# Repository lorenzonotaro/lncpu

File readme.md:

# lncpu

LNCPU is a design for a hobby 8-bit processor. 

## Project structure

Overview of the repository:
* [`v1`](v1) is the first implementation of the lncpu. Here you will find the Logisim simulation and the KiCad project (currently under construction), as well as the Python script for generating the control unit EEPROMS.

* [`lnc`](lnc) is an assembler and C compiler written in Java for the lncpu. It is kept up to date with the current implementation.

* [`eeprom-serial-loader`](eeprom-serial-loader) is a utility program for editing binary data and loading it to/from EEPROMS.

* [`lncpu-emu`](lncpu-emu) is a simple emulator for the lncpu written in C.

* [`lnfsutils`](lnfsutils) is a utility program for working with the lnfs filesystem, a simple FS designed to work on the lncpu.

* [`Programs`](Programs) contains some sample programs you can assemble and run on the lncpu as well as Notmon, a utility program strongly inspired in its functionality (and name) by Wozmon, made by Steve Wozniak for his Apple I.

* [`extras`](extras) contains some additional tools, such as a VsCode extension for lnasm.

## Current state of the project

* **Physical implementation**: work in progress. The Logisim simulation is basically done and tested. Some adjustments to the architecture may still be made, but the main design is complete. The KiCad project is under construction, and it might be necessary to properly simulate the design with actual hardware simulation software (e.g. an HDL simulation) before implementing it physically.

* **Assembler and C compiler**: the assembler is basically complete and stable. The C compiler is still a work in progress, but it is already usable for small-medium sized programs. Arrays and structs are yet to be implemented. The register allocator is very basic and can be improved and general optimization passes in the various stages would be very beneficial for an inefficient architecture like this one.

* **EEPROM editor and loader**: the utility is basically complete and stable. Some improvements can be made to the UI, but it is already usable. More loaders other than the AT28C64 can be added.

* **Emulator**: The emulator is also basically done, but it is very basic and can be improved a lot. It is currently Windows-only because of the use of `<conio.h>` for keyboard input, but porting it to Linux or MacOS should be easy.

* **Programs**: A simple BIOS for the lncpu is under development. Notmon is basically complete and stable, but more features can be added.

* **Extras**: The VsCode extension has syntax highlighting and basic symbol support for lnasm files. More features can be added, such as code snippets and integration with lnc.

## Building

### Prerequisites

- [Maven](https://maven.apache.org/) and [JDK 16+](https://www.oracle.com/java/technologies/javase/jdk16-archive-downloads.html) are required for building both `lnc` and `eeprom-serial-loader`.
- [Python 3.x](https://www.python.org/downloads/) is required to generate the EEPROMs for the control unit.
- [Logisim-evolution](https://github.com/logisim-evolution/logisim-evolution) is used to simulate the design.
- Any C compiler and [CMake](https://cmake.org/) to build the emulator (e.g. `gcc`).

**Note**: I suggest using [my fork of Logisim-evolution (logisim-lncpu branch)](https://github.com/lorenzonotaro/logisim-evolution/tree/lncpu-debugger-logisim) to open the Logisim project. It includes useful features like:
- testing environment for the lncpu
- easy loading of all CU EEPROMs at once
- a neat LNCPU debugger

If you're on Linux, `make.sh` will build everything for you. Usage:

    ./make.sh [--no-eeproms] [--no-eeprom-serial-loader|--no-esl] [--no-lnc] [--no-lnfs|--no-lnfs-utils]

If you're on Windows, use `make.bat` instead. Usage:

    ./make.bat [--no-eeproms] [--no-eeprom-serial-loader|--no-esl] [--no-lnc] [--no-lnfs|--no-lnfs-utils]

These scripts will create an `output` folder containing:
- `lnc.jar`: the assembler and C compiler along with `lnc.bat`/`lnc.sh` scripts for easy usage
- `eeprom-serial-loader.jar`: the EEPROM editing and loading utility along with `eeprom-serial-loader.bat`/`eeprom-serial-loader.sh` scripts for easy usage
- `lncpu-emu.exe`: the LNCPU emulator executable
- `eeproms`: a folder containing all the generated control unit EEPROMs (if you have my fork of Logisim, you may open the Logisim project, then go to Simulate -> Debug LNCPU -> Load CU EEPROMS and select this folder to load them all at once).
- a `lib` folder containing libraries for lnc/lnasm

It is recommended to add the `output` folder to your PATH environment variable for easy usage of `lnc` and `eeprom-serial-loader` from any location and allow the Logisim debugger to compile and load programs directly.

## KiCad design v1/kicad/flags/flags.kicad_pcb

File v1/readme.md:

_This page is a work in progress._

# lncpu v1

v1 is the current implementation of the lncpu.

## Clock cycle

The clock cycle is divided in two phases: Φ1 (control phase) and Φ2 (data phase).

* During Φ1, the data bus contains the contents of `[CS:PC]`: only the device mapped to the memory section containing address `CS:PC` is allowed to write to the data bus, regardless of control signals.

* During Φ2, bus control is determined by the control signals of the current microinstruction.

Each phase has a clock pulse entirely within it, and components may synchronize at the rising edge or the falling edge of each clock pulse.

From Φ and the base clock, 4 rising edges are derived:
* **C1** (Φ1), _control_: the next instruction or microinstruction is loaded and the control signals are stabilized.
* **C2** (Φ1), _fetch_: if required by the current microinstruction, data is moved from `[CS:PC]` to the data latch register via the data bus.
* **C3** (Φ2), _data_: data is transferred between the activated components via the data bus.
* **C4** (Φ2), _increment_: counters such as `CS:PC`, `SP` are incremented/decremented as specified by the current microinstruction.

# Pipeline

The implementation uses a very simple pipeline to spare a few clock cycles.

1. At the beginning of the first clock cycle of any instruction (i.e. when Φ1 goes high), the following conditions are required: 

    * `Data latch (DL)` must contain the **value of the instruction about to be executed**.
    * `CS:PC` must contain the the address of the byte **after the opcode about to be executed**.

*Every instruction (including break, jump and call instructions) must pass to the next with this configuration*.

2. During the execution of the instruction:

    1. `Data latch (DL)` will be loaded with the value pointed to by `CS:PC` (i.e. either the next opcode or the next byte to be fetched by the instruction), then
    2. `CS:PC` will be incremented to point to the byte that will be fetched during the next clock cycle.

# General purpose registers
The CPU has 4 general-purpose 8-bit registers, named `RA`, `RB`, `RC`, and `RD`. These registers can be used to store data and are used by most instructions.

Some registers have special purposes:
* `RA` has left and right shift capabilities, and is used by the `shl` and `shr` instructions.
* `RC` and `RD` are used in combination with the `ircrd` addressing mode to read and write data from the address space.
* `RD` is the only register that can be used to read and write dynamic data to and from `SS`, `SP` and `BP` registers (this is due to the limited number of opcodes available with a 1-byte instruction).

# Jump instructions
The CPU supports several jump instructions that allow the program to change the flow of execution. Each instruction (except `lcall`) is available in two variants, a short and a long variant. The short variant uses a 1-byte immediate value as the target address and loads it into `PC` (without touching `CS`), while the long variant uses a 2-byte absolute address as the target address and loads it into `CS:PC`. 
Short jumps require one less clock cycle than long jumps, so they are preferred when the target address is known at compile time and is within the same code segment as the jump instruction.

The jump instructions are:
| Instruction | Short variant | Long variant | Description |
|-------------|---------------|--------------|-------------|
| Go to | `goto` | `lgoto` | Jumps to the specified address. |
| Jump if carry | `jc` | `ljc` | Jumps to the specified address if the carry flag is set. |
| Jump if zero | `jz` | `ljz` | Jumps to the specified address if the zero flag is set. |
| Jump if negative | `jn` | `ljn` | Jumps to the specified address if the negative flag is set. |
| Call | *not available* | `lcall` | Jumps to the specified address and pushes the current `CS:PC` onto the stack. |

# ALU and FLAGS

The CPU has a simple arithmetic logic unit (ALU) that can perform basic arithmetic and logical operations. The ALU can perform the following operations:
| Operation | Description |
|-----------|-------------|
| `add`     | Adds the contents of two registers or a register and an immediate value. |
| `sub`     | Subtracts the contents of two registers or a register and an immediate value. |
| `and`     | Performs a bitwise AND operation on the contents of two registers or a register and an immediate value. |
| `or`      | Performs a bitwise OR operation on the contents of two registers or a register and an immediate value. |
| `xor`     | Performs a bitwise XOR operation on the contents of two registers or a register and an immediate value. |
| `not`     | Performs a bitwise NOT operation on the contents of a register. |
| `shl`     | Shifts the contents of a register left by 1 bit (multiplying by 2). Only available for `RA`. |
| `shr`     | Shifts the contents of a register right by 1 bit (dividing by 2). Only available for `RA`. |
| `inc`     | Increments the contents of a register by 1. |
| `dec`     | Decrements the contents of a register by 1. |

The ALU also sets the `FLAGS` register based on the result of the operation. The `FLAGS` register is a 4-bit register that contains the following flags (least significant bit first):
| Flag | Description |
|------|-------------|
| `C` | Carry flag, set to 1 if the result of an addition or subtraction operation causes an overflow. |
| `Z` | Zero flag, set to 1 if the result of an operation is 0. |
| `N` | Negative flag, set to 1 if the result of an operation is negative (i.e. the most significant bit is set). |
| `I` | Interrupt disable flag, set to 1 if interrupts are disabled (not modified by ALU operations) |

The `CZN` flags can be used to control the flow of the program with conditional jump instructions. The `I` flag is used to enable or disable interrupts, as described in the [Interrupts](#interrupts) section.

The `C` flag can be manually set or cleared with the `sec` (set carry) and `clc` (clear carry) instructions, respectively.

# Address space
The address bus is 16-bits wide, allowing for a total of 65536 bytes of addressable memory. The address space is divided in 8 "devices"; the top 3 bits of the address bus are used to select the device, while the bottom 13 bits are used to select the address within that device.
The address space is divided as follows:
| Device | Address range | Description |
|--------|---------------|-------------|
| ROM    | 0x0000 - 0x1FFF | Read-only memory, points to the extractable chip that can be loaded with a program. |
| RAM    | 0x2000 - 0x3FFF | Read-write memory, used for data storage. |
| D0     | 0x4000 - 0x5FFF | Device 1, can be used for any purpose. |
| D1     | 0x6000 - 0x7FFF | Device 2, can be used for any purpose. |
| D2     | 0x8000 - 0x9FFF | Device 3, can be used for any purpose. |
| D3     | 0xA000 - 0xBFFF | Device 4, can be used for any purpose. |
| D4     | 0xC000 - 0xDFFF | Device 5, can be used for any purpose. |
| D5     | 0xE000 - 0xFFFF | Device 6, can be used for any purpose. |

# Stack

The implementation includes a basic stack setup:

* the 8-bit `SS` register contains the page that will contain the stack (i.e. the top 8-bits of the current stack pointer).

* the 8-bit `SP` register points to the **next available stack position** in the stack page.

The top of the stack is pointed to by `SS:SP`. The stack **grows upwards**: `push` operations move a value into `[SS:SP]` and increment the stack by 1; `pop` operations read the value from `[SS:SP]` and decrement the stack by 1.

Calls and interrupts will push the current `CS:PC` onto the stack, so that it can be restored later. It is the programmer's responsibility to load `SS` and `SP` with correct values before using stack manipulation instructions and/or calls, and to ensure that the stack does not overflow, as the implementation does not include any stack overflow checks.

To function properly, the stack obviously needs to be located in a location in the address space that is writable and readable by the CPU (usually in memory, but it can also be in any device that supports reading and writing). See the [Address space](#address-space) section for more information.

The `BP` register points to the base of the current stack frame. It is not updated along with SP, so it can be used to access local variables in the current stack frame. It is the programmer's responsibility to ensure that `BP` is set correctly before using it.
It is used by some instructions to access local variables in the current stack frame, with an addressing mode known as `ibpoffset` (base pointer offset, e.g. `[BP+1]` to access the first local variable in the current stack frame).

# Data segment
The data segment is a 256-byte segment that is used to store frequently used data by some instructions that use `dpage` addressing mode and that require one less clock cycle. 
The `DS` register points to the data segment, containing the top 8-bits of the data segment's start address.
The data segment can be located anywhere in the address space, but it is recommended to place it in the RAM device (0x2000 - 0x3FFF) to ensure that it is writable and readable by the CPU.

# Interrupts
The implementation includes a basic interrupt system that allows the CPU to handle interrupts from devices.

Devices can signal an interrupt by pulling the `~IRQ` line low. Instead of loading the next instruction, at the end of the current instruction, the CPU will push the current `CS:PC` and the current `FLAGS` register value onto the stack and load the `CS:PC` with the value `0x1F00` (the interrupt vector address, last page of ROM). This is the address where the interrupt handler is located, and it is the programmer's responsibility to ensure that the interrupt handler is loaded there.

The interrupt handler is a piece of code that will handle the interrupt and return control to the CPU when it is done via the `iret` instruction.
The interrupt handler must detect which device signaled the interrupt and handle it accordingly and must communicate with that device to acknowledge the interrupt and clear it (otherwise the device will keep signaling the interrupt and the CPU will keep handling it, causing an infinite loop).

Interrupts can be disabled with the `sid` (set interrupt disable) instruction, which will set the `I` flag in the `FLAGS` register to 1. This will prevent the CPU from handling interrupts until the `cid` (clear interrupt disable) instruction is executed, which will clear the `I` flag in the `FLAGS` register to 0.

# Addressing modes
The CPU supports several addressing modes, which determine how the operands of an instruction are accessed. The addressing modes are:
| Addressing mode | Name | Description |
|-----------------|------|-------------|
| `immediate`     | Immediate | The operand is a constant value, specified as an operand to the instruction. |
| `abs`        | Absolute | The operand is a 2-byte address of a location in the address space, provided as an operand to the instruction. |
| `dpage`      | Data page | The operand is a 1-byte offset (specified as an operand to the instruction) from the data segment, which is specified in the `DS` register. |
| `ibpoffset`  | Stack frame | The operand is a 1-byte offset (specified as an operand to the instruction) from the stack base pointer, which is specified in the `BP` register. |
| `ird`        | Data page indirect | Requires no operands, the location is in the data page at the address specified by the contents of the `RD` register. |
| `ircrd` | Full indirect | Requires no operands, the location is specified by the contents of the RC and RD registers.

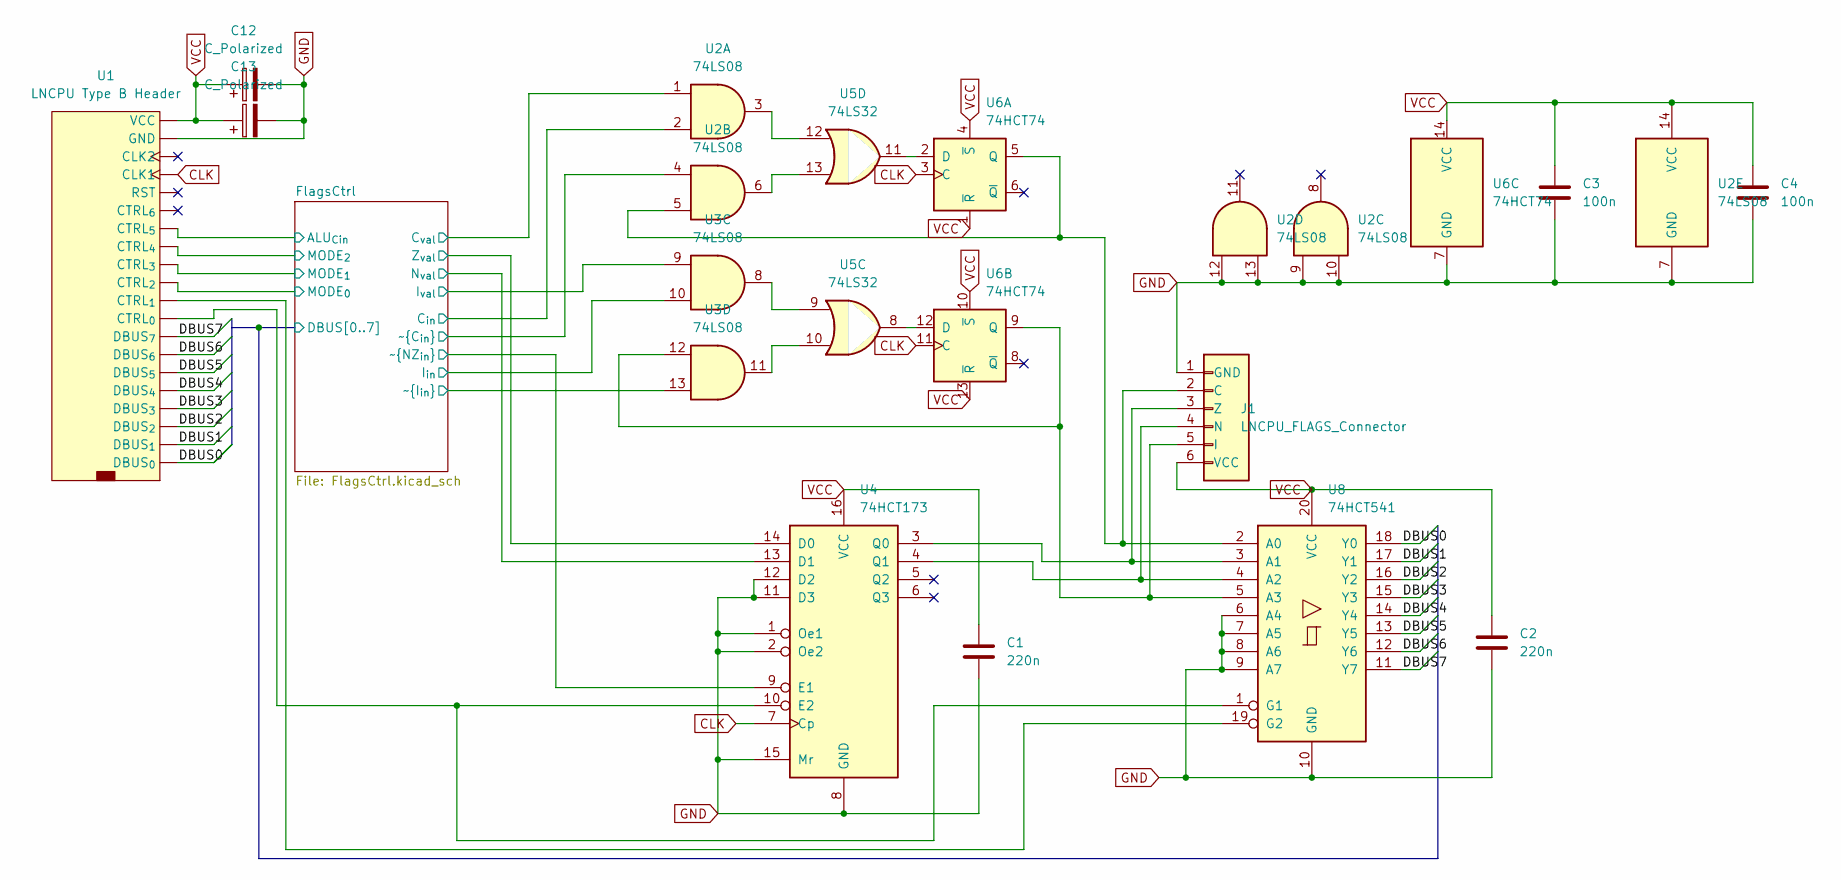
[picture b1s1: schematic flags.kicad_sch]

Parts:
C1, C2: 220n; C_Disc_D5.0mm_W2.5mm_P2.50mm
C3, C4: 100n; C_Disc_D5.0mm_W2.5mm_P2.50mm
C12: C_Polarized; CP_Radial_D5.0mm_P2.00mm
C13: C_Polarized; CP_Radial_D4.0mm_P2.00mm-Large-Holes
J1: LNCPU_FLAGS_Connector; PinSocket_1x06_P2.54mm_Vertical
U1: LNCPU Type B Header; LNCPU_Type_B_Header
U2, U3: 74LS08; DIP-14_W7.62mm_LongPads
U4: 74HCT173; DIP-16_W7.62mm_LongPads
U5: 74LS32; DIP-14_W7.62mm_LongPads
U6: 74HCT74; DIP-14_W7.62mm_LongPads
U8: 74HCT541; DIP-20_W7.62mm_LongPads

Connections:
/FlagsCtrl/ALU_{Cin}: U1.14 (CTRL_{5}); also elsewhere on the board
/FlagsCtrl/C_{val}: U2.1; also elsewhere on the board
/FlagsCtrl/DBUS0: U1.3 (DBUS_{0}), U8.18 (Y0); also elsewhere on the board
/FlagsCtrl/DBUS1: U1.5 (DBUS_{1}), U8.17 (Y1); also elsewhere on the board
/FlagsCtrl/DBUS2: U1.7 (DBUS_{2}), U8.16 (Y2); also elsewhere on the board
/FlagsCtrl/DBUS3: U1.9 (DBUS_{3}), U8.15 (Y3); also elsewhere on the board
/FlagsCtrl/DBUS4: U1.11 (DBUS_{4}), U8.14 (Y4); also elsewhere on the board
/FlagsCtrl/DBUS5: U1.13 (DBUS_{5}), U8.13 (Y5); also elsewhere on the board
/FlagsCtrl/DBUS6: U1.15 (DBUS_{6}), U8.12 (Y6); also elsewhere on the board
/FlagsCtrl/DBUS7: U1.17 (DBUS_{7}), U8.11 (Y7); also elsewhere on the board
/FlagsCtrl/I_{in}: U3.10; also elsewhere on the board
/FlagsCtrl/I_{val}: U3.9; also elsewhere on the board
/FlagsCtrl/MODE_{0}: U1.8 (CTRL_{2}); also elsewhere on the board
/FlagsCtrl/MODE_{1}: U1.10 (CTRL_{3}), U2.2; also elsewhere on the board
/FlagsCtrl/MODE_{2}: U1.12 (CTRL_{4}); also elsewhere on the board
/FlagsCtrl/N_{val}: U4.13 (D1); also elsewhere on the board
/FlagsCtrl/Z_{val}: U4.14 (D0); also elsewhere on the board
/FlagsCtrl/~I_{in}: U3.13; also elsewhere on the board
/FlagsCtrl/~MODE_{1}: U2.4; also elsewhere on the board
/FlagsCtrl/~NZ_{in}: U4.9 (E1); also elsewhere on the board
CLK: U1.21 (CLK1), U4.7 (Cp), U6.3 (C), U6.11 (C)
GND: C1.2, C2.2, C3.2, C4.2, C12.2, C13.2, J1.1 (GND), U1.1 (GND), U1.18 (GND), U1.22 (GND), U1.23 (GND), U2.7 (GND), U2.9, U2.10, U2.12, U2.13, U4.1 (Oe1), U4.2 (Oe2), U4.8 (GND), U4.11 (D3), U4.12 (D2), U4.15 (Mr), U6.7 (GND), U8.6 (A4), U8.7 (A5), U8.8 (A6), U8.9 (A7), U8.10 (GND); also elsewhere on the board
unnamed: J1.2 (C), U2.5, U6.5 (Q), U8.2 (A0)
unnamed: J1.5 (I), U3.12, U6.9 (Q), U8.5 (A3)
unnamed: J1.4 (N), U4.4 (Q1), U8.4 (A2)
unnamed: J1.3 (Z), U4.3 (Q0), U8.3 (A1)
unnamed: U1.4 (CTRL_{0}), U4.10 (E2), U8.1 (G1)
unnamed: U1.6 (CTRL_{1}), U8.19 (G2)
unnamed: U2.3, U5.12
unnamed: U2.6, U5.13
unnamed: U3.8, U5.9
unnamed: U3.11, U5.10
unnamed: U5.11, U6.2 (D)
unnamed: U5.8, U6.12 (D)
VCC: C1.1, C2.1, C3.1, C4.1, C12.1, C13.1, J1.6 (VCC), U1.2 (VCC), U1.24 (VCC), U2.14 (VCC), U4.16 (VCC), U6.1 (~R), U6.4 (~S), U6.10 (~S), U6.13 (~R), U6.14 (VCC), U8.20 (VCC); also elsewhere on the board

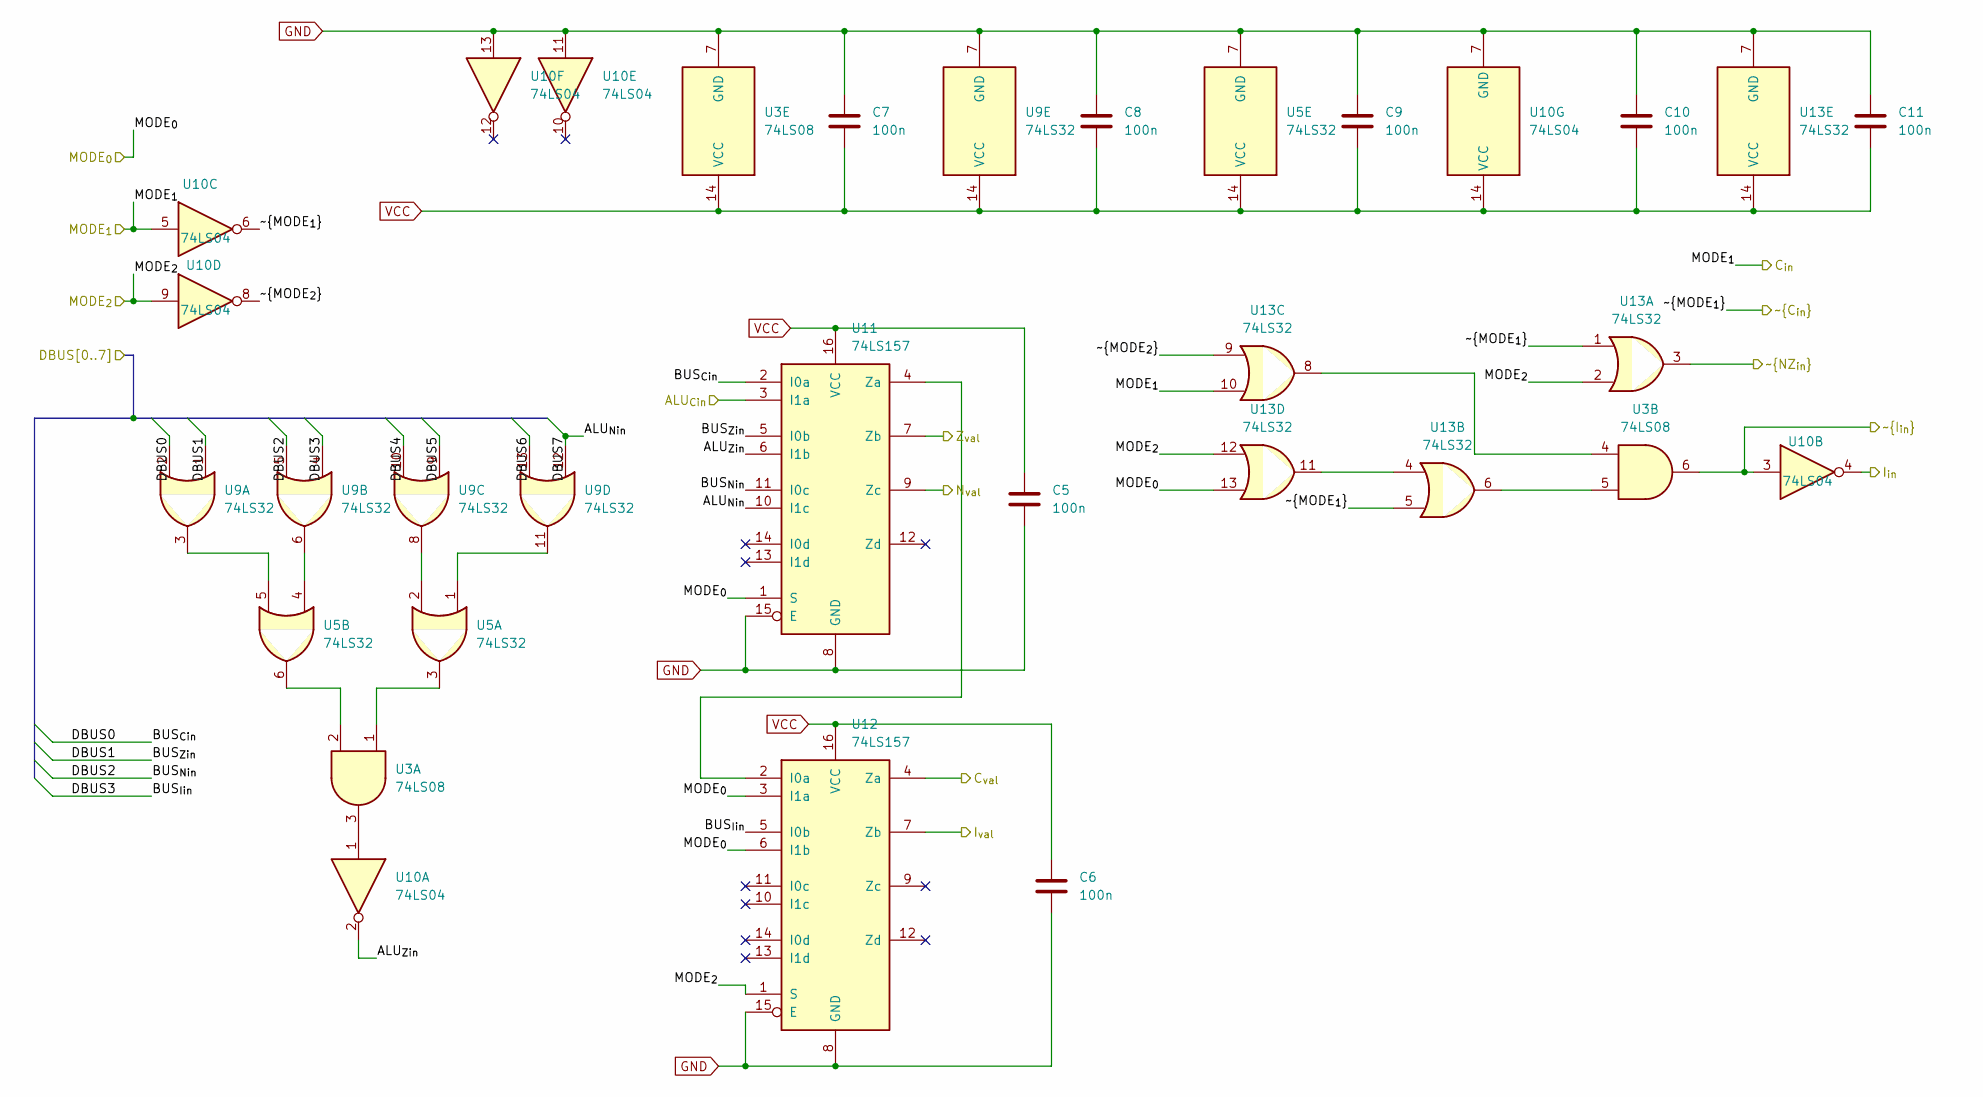
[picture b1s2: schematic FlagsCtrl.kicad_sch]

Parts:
C5, C6, C7, C8, C9, C10, C11: 100n; C_Disc_D5.0mm_W2.5mm_P2.50mm
U3: 74LS08; DIP-14_W7.62mm_LongPads
U5, U9, U13: 74LS32; DIP-14_W7.62mm_LongPads
U10: 74LS04; DIP-14_W7.62mm_LongPads
U11, U12: 74LS157; DIP-16_W7.62mm_LongPads

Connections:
/FlagsCtrl/ALU_{Cin}: U11.3 (I1a); also elsewhere on the board
/FlagsCtrl/ALU_{Zin}: U10.2, U11.6 (I1b)
/FlagsCtrl/C_{val}: U12.4 (Za); also elsewhere on the board
/FlagsCtrl/DBUS0: U9.2, U11.2 (I0a); also elsewhere on the board
/FlagsCtrl/DBUS1: U9.1, U11.5 (I0b); also elsewhere on the board
/FlagsCtrl/DBUS2: U9.5, U11.11 (I0c); also elsewhere on the board
/FlagsCtrl/DBUS3: U9.4, U12.5 (I0b); also elsewhere on the board
/FlagsCtrl/DBUS4: U9.10; also elsewhere on the board
/FlagsCtrl/DBUS5: U9.9; also elsewhere on the board
/FlagsCtrl/DBUS6: U9.13; also elsewhere on the board
/FlagsCtrl/DBUS7: U9.12, U11.10 (I1c); also elsewhere on the board
/FlagsCtrl/I_{in}: U10.4; also elsewhere on the board
/FlagsCtrl/I_{val}: U12.7 (Zb); also elsewhere on the board
/FlagsCtrl/MODE_{0}: U11.1 (S), U12.3 (I1a), U12.6 (I1b), U13.13; also elsewhere on the board
/FlagsCtrl/MODE_{1}: U10.5, U13.10; also elsewhere on the board
/FlagsCtrl/MODE_{2}: U10.9, U12.1 (S), U13.2, U13.12; also elsewhere on the board
/FlagsCtrl/N_{val}: U11.9 (Zc); also elsewhere on the board
/FlagsCtrl/Z_{val}: U11.7 (Zb); also elsewhere on the board
/FlagsCtrl/~I_{in}: U3.6, U10.3; also elsewhere on the board
/FlagsCtrl/~MODE_{1}: U10.6, U13.1, U13.5; also elsewhere on the board
/FlagsCtrl/~MODE_{2}: U10.8, U13.9
/FlagsCtrl/~NZ_{in}: U13.3; also elsewhere on the board
GND: C5.2, C6.2, C7.1, C8.1, C9.1, C10.1, C11.1, U3.7 (GND), U5.7 (GND), U9.7 (GND), U10.7 (GND), U10.11, U10.13, U11.8 (GND), U11.15 (E), U12.8 (GND), U12.15 (E), U13.7 (GND); also elsewhere on the board
unnamed: U3.1, U5.3
unnamed: U3.2, U5.6
unnamed: U5.1, U9.11
unnamed: U5.2, U9.8
unnamed: U5.4, U9.6
unnamed: U5.5, U9.3
unnamed: U3.3, U10.1
unnamed: U11.4 (Za), U12.2 (I0a)
unnamed: U3.5, U13.6
unnamed: U3.4, U13.8
unnamed: U13.4, U13.11
VCC: C5.1, C6.1, C7.2, C8.2, C9.2, C10.2, C11.2, U3.14 (VCC), U5.14 (VCC), U9.14 (VCC), U10.14 (VCC), U11.16 (VCC), U12.16 (VCC), U13.14 (VCC); also elsewhere on the board

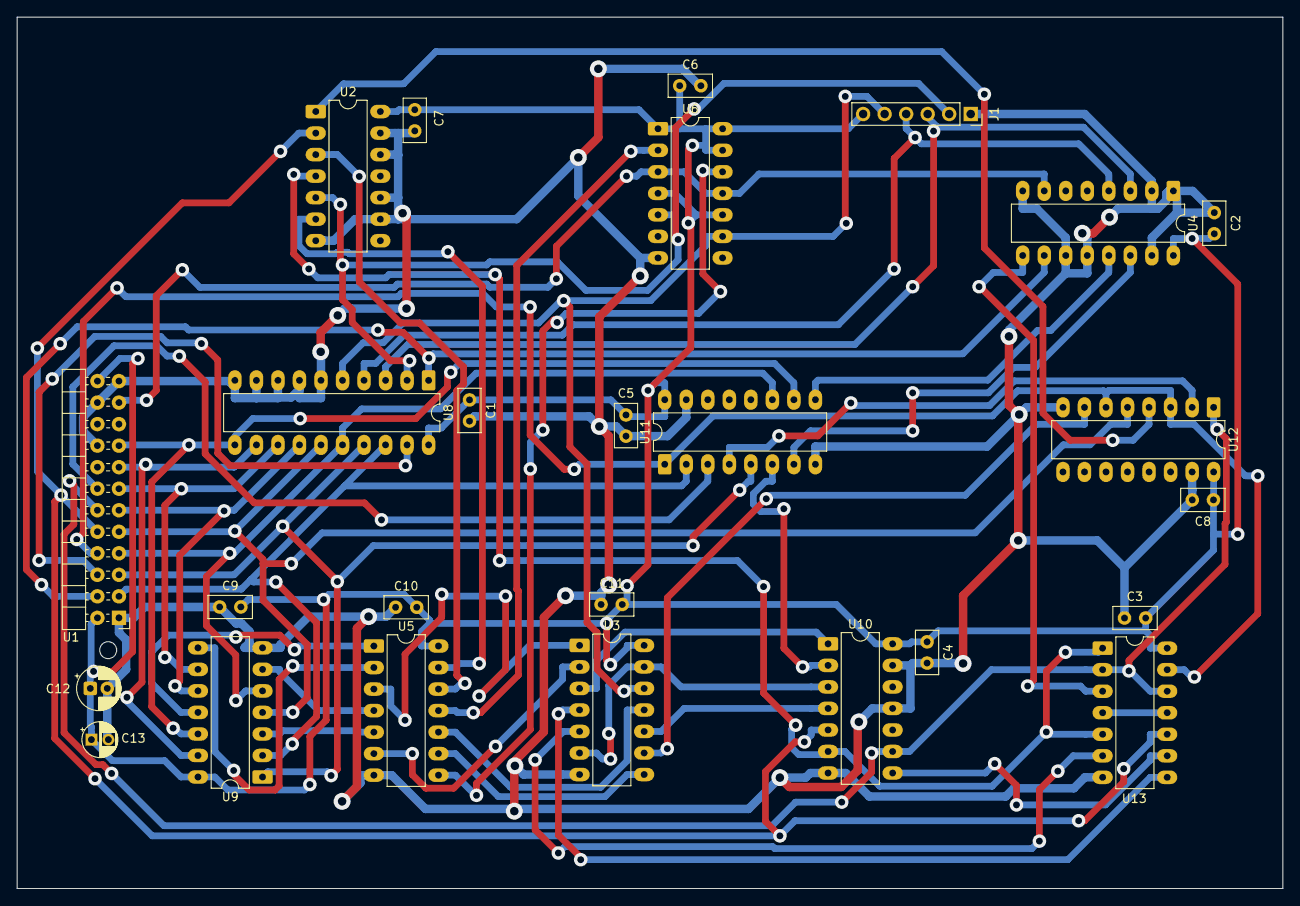
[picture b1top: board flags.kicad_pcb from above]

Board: 2 copper layers, 149.4 x 102.8 mm, 26 parts (0 on the bottom side), 48 nets.

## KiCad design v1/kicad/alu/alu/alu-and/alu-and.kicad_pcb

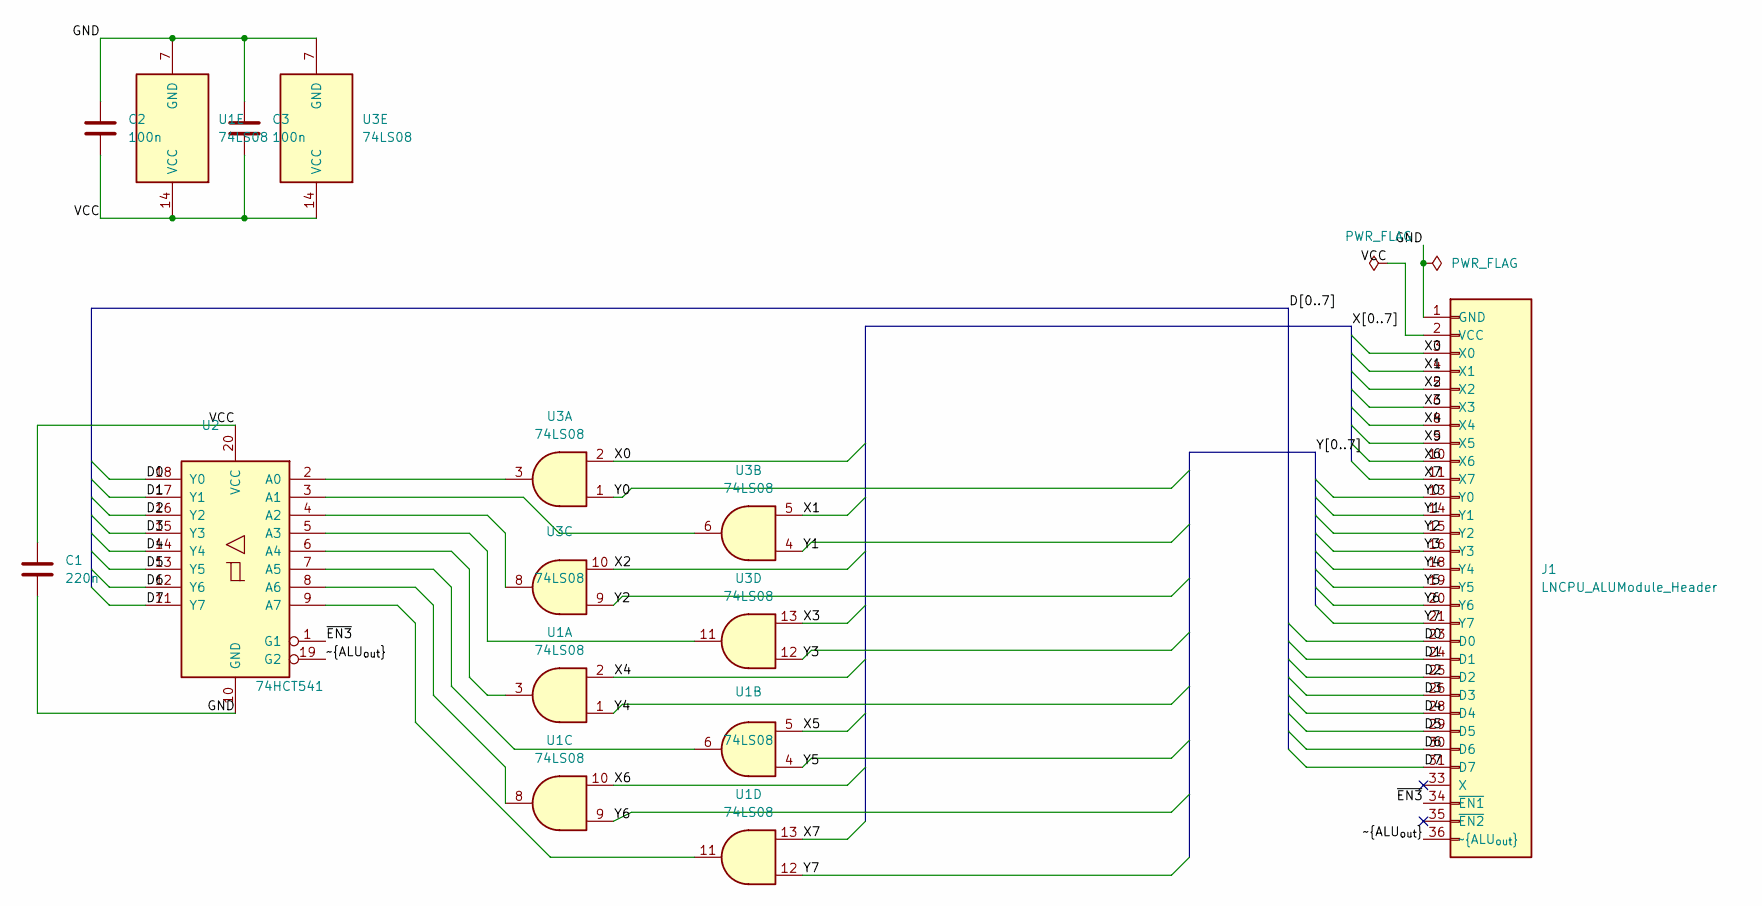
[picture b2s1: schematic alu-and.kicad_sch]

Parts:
C1: 220n; C_Disc_D5.0mm_W2.5mm_P5.00mm
C2, C3: 100n; C_Disc_D5.0mm_W2.5mm_P5.00mm
J1: LNCPU_ALUModule_Header; LNCPU_ALU_Module_Header
U1, U3: 74LS08; DIP-14_W7.62mm_LongPads
U2: 74HCT541; DIP-20_W7.62mm_LongPads

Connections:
/D0: J1.23 (D0), U2.18 (Y0)
/D1: J1.24 (D1), U2.17 (Y1)
/D2: J1.25 (D2), U2.16 (Y2)
/D3: J1.26 (D3), U2.15 (Y3)
/D4: J1.28 (D4), U2.14 (Y4)
/D5: J1.29 (D5), U2.13 (Y5)
/D6: J1.30 (D6), U2.12 (Y6)
/D7: J1.31 (D7), U2.11 (Y7)
/GND: C1.2, C2.1, C3.1, J1.1 (GND), J1.7 (GND), J1.12 (GND), J1.17 (GND), J1.22 (GND), J1.27 (GND), J1.32 (GND), J1.37 (GND), U1.7 (GND), U2.10 (GND), U3.7 (GND)
/VCC: C1.1, C2.2, C3.2, J1.2 (VCC), J1.38 (VCC), U1.14 (VCC), U2.20 (VCC), U3.14 (VCC)
/X0: J1.3 (X0), U3.2
/X1: J1.4 (X1), U3.5
/X2: J1.5 (X2), U3.10
/X3: J1.6 (X3), U3.13
/X4: J1.8 (X4), U1.2
/X5: J1.9 (X5), U1.5
/X6: J1.10 (X6), U1.10
/X7: J1.11 (X7), U1.13
/Y0: J1.13 (Y0), U3.1
/Y1: J1.14 (Y1), U3.4
/Y2: J1.15 (Y2), U3.9
/Y3: J1.16 (Y3), U3.12
/Y4: J1.18 (Y4), U1.1
/Y5: J1.19 (Y5), U1.4
/Y6: J1.20 (Y6), U1.9
/Y7: J1.21 (Y7), U1.12
/~ALU_{out}: J1.36 (~ALU_{out}), U2.19 (G2)
/~EN3: J1.34 (~EN1), U2.1 (G1)
unnamed: U2.2 (A0), U3.3
unnamed: U2.3 (A1), U3.6
unnamed: U2.4 (A2), U3.8
unnamed: U2.5 (A3), U3.11
unnamed: U1.3, U2.6 (A4)
unnamed: U1.6, U2.7 (A5)
unnamed: U1.8, U2.8 (A6)
unnamed: U1.11, U2.9 (A7)

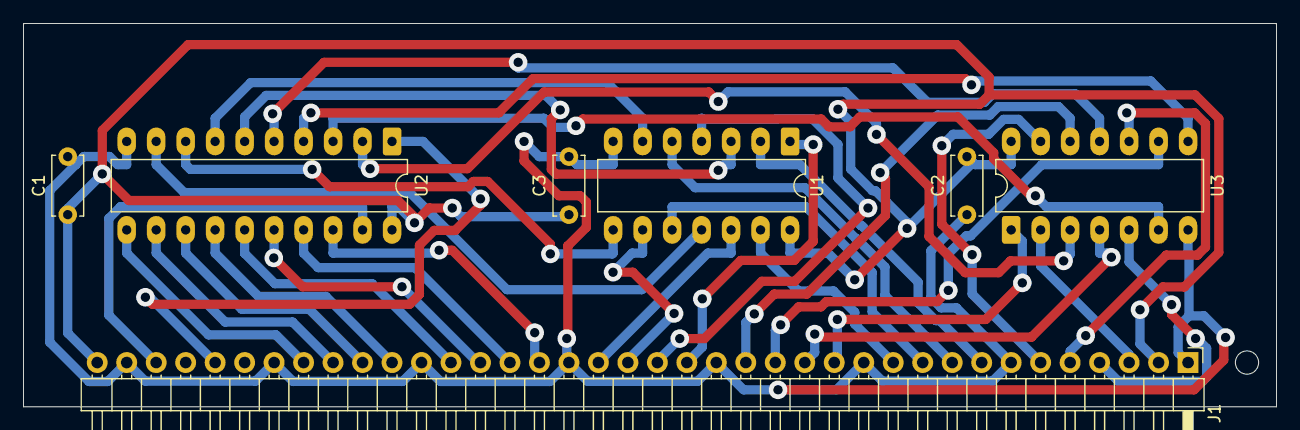
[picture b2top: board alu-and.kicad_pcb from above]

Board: 2 copper layers, 108.0 x 33.0 mm, 7 parts (0 on the bottom side), 36 nets.

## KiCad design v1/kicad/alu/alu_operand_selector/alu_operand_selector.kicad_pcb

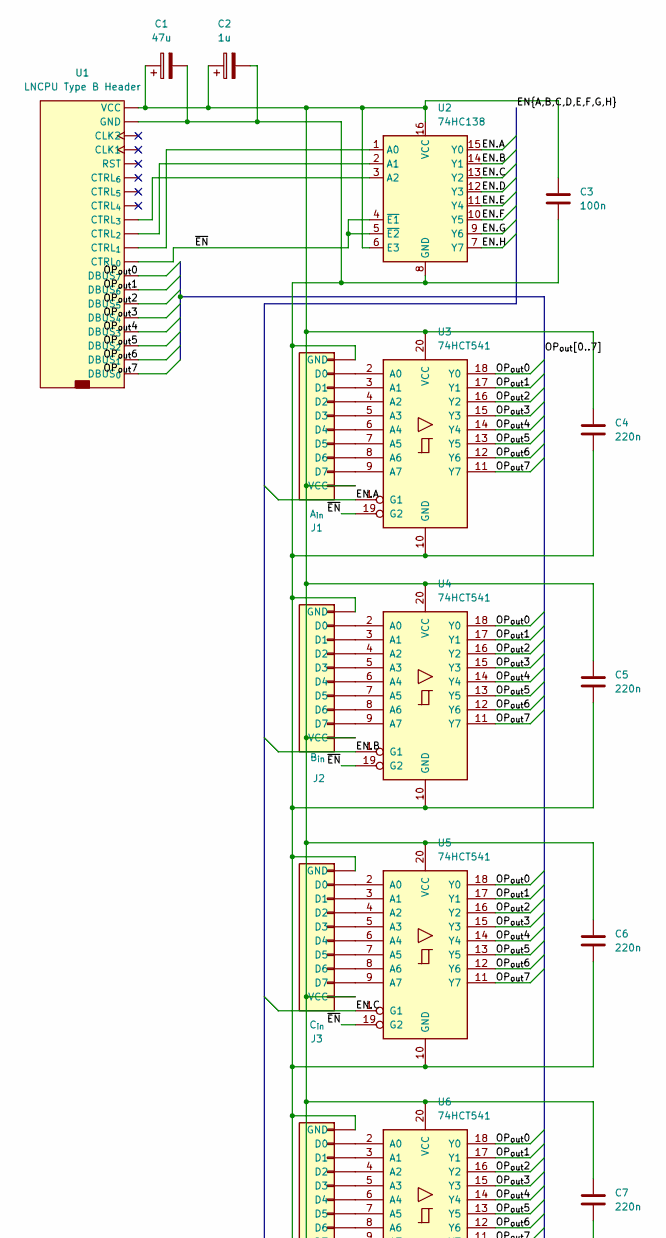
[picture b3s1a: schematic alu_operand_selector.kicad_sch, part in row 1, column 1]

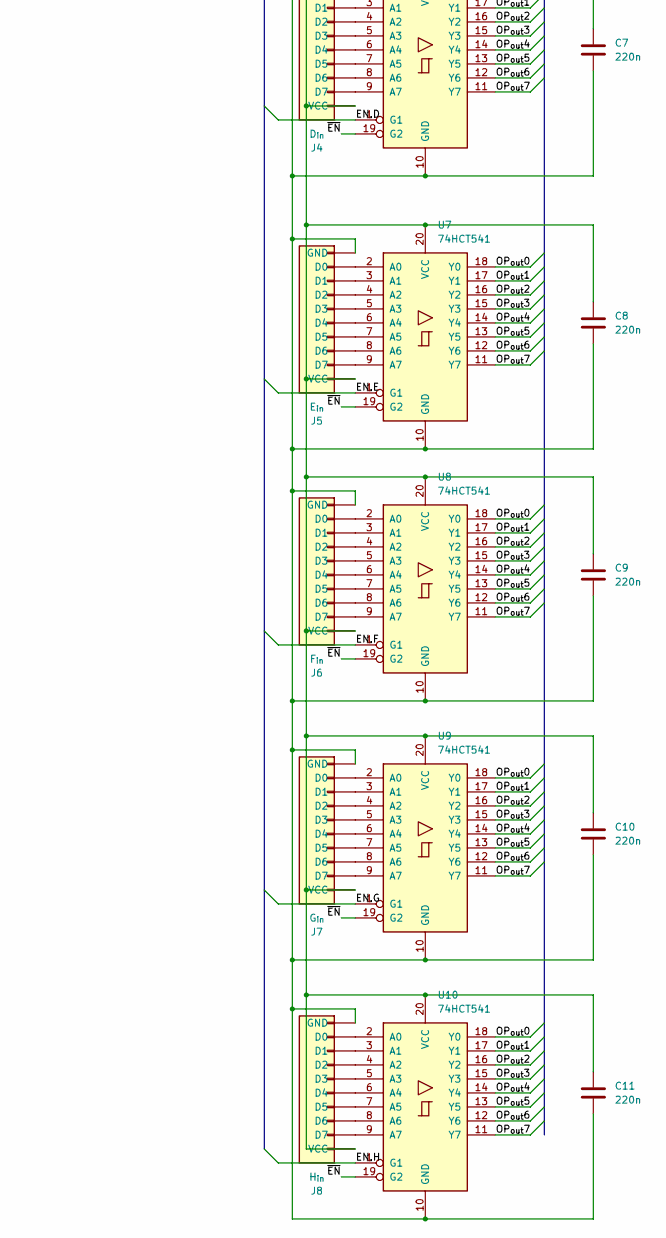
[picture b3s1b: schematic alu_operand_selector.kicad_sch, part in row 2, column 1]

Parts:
C1: 47u; CP_Radial_D5.0mm_P2.00mm
C2: 1u; CP_Radial_D4.0mm_P2.00mm-Large-Holes
C3: 100n; C_Disc_D5.0mm_W2.5mm_P2.50mm
C4, C5, C6, C7, C8, C9, C10, C11: 220n; C_Disc_D5.0mm_W2.5mm_P2.50mm
J1: A_{in}; PinSocket_1x10_P2.54mm_Vertical
J2: B_{in}; PinSocket_1x10_P2.54mm_Vertical
J3: C_{in}; PinSocket_1x10_P2.54mm_Vertical
J4: D_{in}; PinSocket_1x10_P2.54mm_Vertical
J5: E_{in}; PinSocket_1x10_P2.54mm_Vertical
J6: F_{in}; PinSocket_1x10_P2.54mm_Vertical
J7: G_{in}; PinSocket_1x10_P2.54mm_Vertical
J8: H_{in}; PinSocket_1x10_P2.54mm_Vertical
U1: LNCPU Type B Header; LNCPU_Type_B_Header
U2: 74HC138; DIP-16_W7.62mm_LongPads
U3, U4, U5, U6, U7, U8, U9, U10: 74HCT541; DIP-20_W7.62mm_LongPads

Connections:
/EN.A: U2.15 (Y0), U3.1 (G1)
/EN.B: U2.14 (Y1), U4.1 (G1)
/EN.C: U2.13 (Y2), U5.1 (G1)
/EN.D: U2.12 (Y3), U6.1 (G1)
/EN.E: U2.11 (Y4), U7.1 (G1)
/EN.F: U2.10 (Y5), U8.1 (G1)
/EN.G: U2.9 (Y6), U9.1 (G1)
/EN.H: U2.7 (Y7), U10.1 (G1)
/OP_{out}0: U1.17 (DBUS_{7}), U3.18 (Y0), U4.18 (Y0), U5.18 (Y0), U6.18 (Y0), U7.18 (Y0), U8.18 (Y0), U9.18 (Y0), U10.18 (Y0)
/OP_{out}1: U1.15 (DBUS_{6}), U3.17 (Y1), U4.17 (Y1), U5.17 (Y1), U6.17 (Y1), U7.17 (Y1), U8.17 (Y1), U9.17 (Y1), U10.17 (Y1)
/OP_{out}2: U1.13 (DBUS_{5}), U3.16 (Y2), U4.16 (Y2), U5.16 (Y2), U6.16 (Y2), U7.16 (Y2), U8.16 (Y2), U9.16 (Y2), U10.16 (Y2)
/OP_{out}3: U1.11 (DBUS_{4}), U3.15 (Y3), U4.15 (Y3), U5.15 (Y3), U6.15 (Y3), U7.15 (Y3), U8.15 (Y3), U9.15 (Y3), U10.15 (Y3)
/OP_{out}4: U1.9 (DBUS_{3}), U3.14 (Y4), U4.14 (Y4), U5.14 (Y4), U6.14 (Y4), U7.14 (Y4), U8.14 (Y4), U9.14 (Y4), U10.14 (Y4)
/OP_{out}5: U1.7 (DBUS_{2}), U3.13 (Y5), U4.13 (Y5), U5.13 (Y5), U6.13 (Y5), U7.13 (Y5), U8.13 (Y5), U9.13 (Y5), U10.13 (Y5)
/OP_{out}6: U1.5 (DBUS_{1}), U3.12 (Y6), U4.12 (Y6), U5.12 (Y6), U6.12 (Y6), U7.12 (Y6), U8.12 (Y6), U9.12 (Y6), U10.12 (Y6)
/OP_{out}7: U1.3 (DBUS_{0}), U3.11 (Y7), U4.11 (Y7), U5.11 (Y7), U6.11 (Y7), U7.11 (Y7), U8.11 (Y7), U9.11 (Y7), U10.11 (Y7)
/~EN: U1.4 (CTRL_{0}), U2.4 (~E1), U2.5 (~E2), U3.19 (G2), U4.19 (G2), U5.19 (G2), U6.19 (G2), U7.19 (G2), U8.19 (G2), U9.19 (G2), U10.19 (G2)
unnamed: J1.2 (D0), U3.2 (A0)
unnamed: J1.3 (D1), U3.3 (A1)
unnamed: J1.4 (D2), U3.4 (A2)
unnamed: J1.5 (D3), U3.5 (A3)
unnamed: J1.6 (D4), U3.6 (A4)
unnamed: J1.7 (D5), U3.7 (A5)
unnamed: J1.8 (D6), U3.8 (A6)
unnamed: J1.9 (D7), U3.9 (A7)
unnamed: C1.2, C2.2, C3.2, C4.2, C5.2, C6.2, C7.2, C8.2, C9.2, C10.2, C11.2, J1.1 (GND), J2.1 (GND), J3.1 (GND), J4.1 (GND), J5.1 (GND), J6.1 (GND), J7.1 (GND), J8.1 (GND), U1.1 (GND), U1.18 (GND), U1.22 (GND), U1.23 (GND), U2.8 (GND), U3.10 (GND), U4.10 (GND), U5.10 (GND), U6.10 (GND), U7.10 (GND), U8.10 (GND), U9.10 (GND), U10.10 (GND)
unnamed: C1.1, C2.1, C3.1, C4.1, C5.1, C6.1, C7.1, C8.1, C9.1, C10.1, C11.1, J1.10 (VCC), J2.10 (VCC), J3.10 (VCC), J4.10 (VCC), J5.10 (VCC), J6.10 (VCC), J7.10 (VCC), J8.10 (VCC), U1.2 (VCC), U1.24 (VCC), U2.6 (E3), U2.16 (VCC), U3.20 (VCC), U4.20 (VCC), U5.20 (VCC), U6.20 (VCC), U7.20 (VCC), U8.20 (VCC), U9.20 (VCC), U10.20 (VCC)
unnamed: J2.2 (D0), U4.2 (A0)
unnamed: J2.3 (D1), U4.3 (A1)
unnamed: J2.4 (D2), U4.4 (A2)
unnamed: J2.5 (D3), U4.5 (A3)
unnamed: J2.6 (D4), U4.6 (A4)
unnamed: J2.7 (D5), U4.7 (A5)
unnamed: J2.8 (D6), U4.8 (A6)
unnamed: J2.9 (D7), U4.9 (A7)
unnamed: J3.2 (D0), U5.2 (A0)
unnamed: J3.3 (D1), U5.3 (A1)
unnamed: J3.4 (D2), U5.4 (A2)
unnamed: J3.5 (D3), U5.5 (A3)
unnamed: J3.6 (D4), U5.6 (A4)
unnamed: J3.7 (D5), U5.7 (A5)
unnamed: J3.8 (D6), U5.8 (A6)
unnamed: J3.9 (D7), U5.9 (A7)
unnamed: J4.2 (D0), U6.2 (A0)
unnamed: J4.3 (D1), U6.3 (A1)
unnamed: J4.4 (D2), U6.4 (A2)
unnamed: J4.5 (D3), U6.5 (A3)
unnamed: J4.6 (D4), U6.6 (A4)
unnamed: J4.7 (D5), U6.7 (A5)
unnamed: J4.8 (D6), U6.8 (A6)
unnamed: J4.9 (D7), U6.9 (A7)
unnamed: J5.2 (D0), U7.2 (A0)
unnamed: J5.3 (D1), U7.3 (A1)
unnamed: J5.4 (D2), U7.4 (A2)
unnamed: J5.5 (D3), U7.5 (A3)
unnamed: J5.6 (D4), U7.6 (A4)
unnamed: J5.7 (D5), U7.7 (A5)
unnamed: J5.8 (D6), U7.8 (A6)
unnamed: J5.9 (D7), U7.9 (A7)
unnamed: J6.2 (D0), U8.2 (A0)
unnamed: J6.3 (D1), U8.3 (A1)
unnamed: J6.4 (D2), U8.4 (A2)
unnamed: J6.5 (D3), U8.5 (A3)
unnamed: J6.6 (D4), U8.6 (A4)
unnamed: J6.7 (D5), U8.7 (A5)
unnamed: J6.8 (D6), U8.8 (A6)
unnamed: J6.9 (D7), U8.9 (A7)
unnamed: J7.2 (D0), U9.2 (A0)
unnamed: J7.3 (D1), U9.3 (A1)
unnamed: J7.4 (D2), U9.4 (A2)
unnamed: J7.5 (D3), U9.5 (A3)
unnamed: J7.6 (D4), U9.6 (A4)
unnamed: J7.7 (D5), U9.7 (A5)
unnamed: J7.8 (D6), U9.8 (A6)
unnamed: J7.9 (D7), U9.9 (A7)
unnamed: J8.2 (D0), U10.2 (A0)
unnamed: J8.3 (D1), U10.3 (A1)
unnamed: J8.4 (D2), U10.4 (A2)
unnamed: J8.5 (D3), U10.5 (A3)
unnamed: J8.6 (D4), U10.6 (A4)
unnamed: J8.7 (D5), U10.7 (A5)
unnamed: J8.8 (D6), U10.8 (A6)
unnamed: J8.9 (D7), U10.9 (A7)
unnamed: U1.6 (CTRL_{1}), U2.1 (A0)
unnamed: U1.8 (CTRL_{2}), U2.2 (A1)
unnamed: U1.10 (CTRL_{3}), U2.3 (A2)

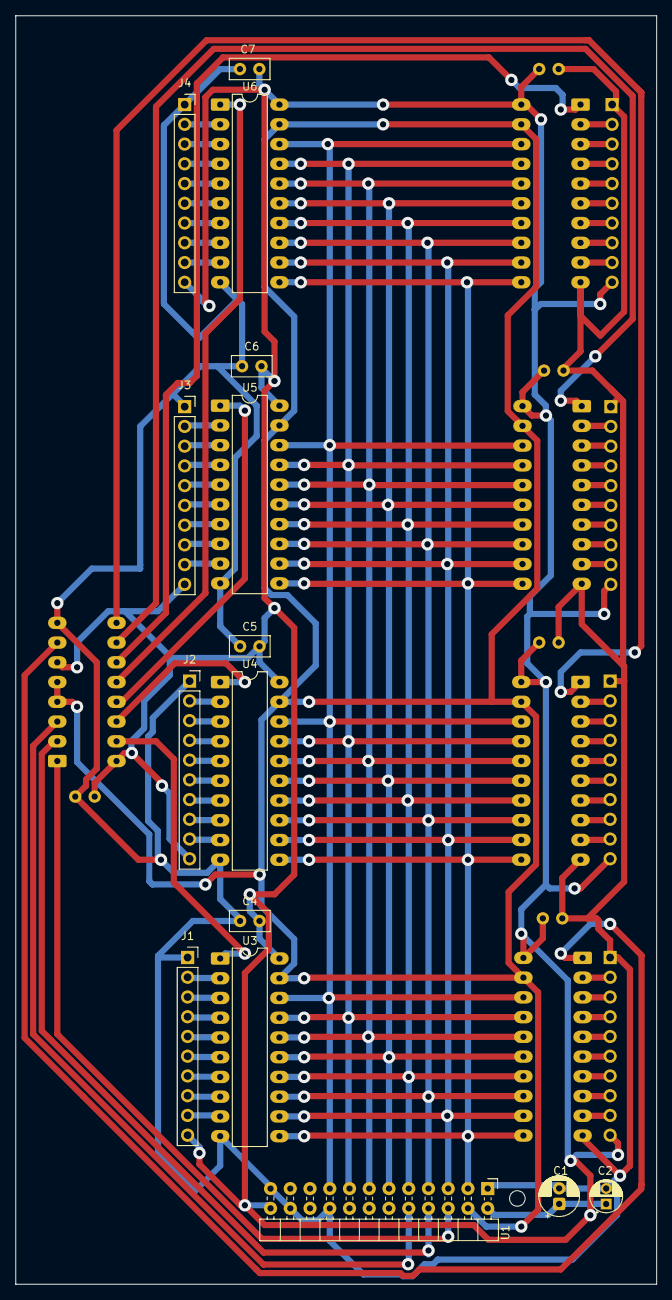
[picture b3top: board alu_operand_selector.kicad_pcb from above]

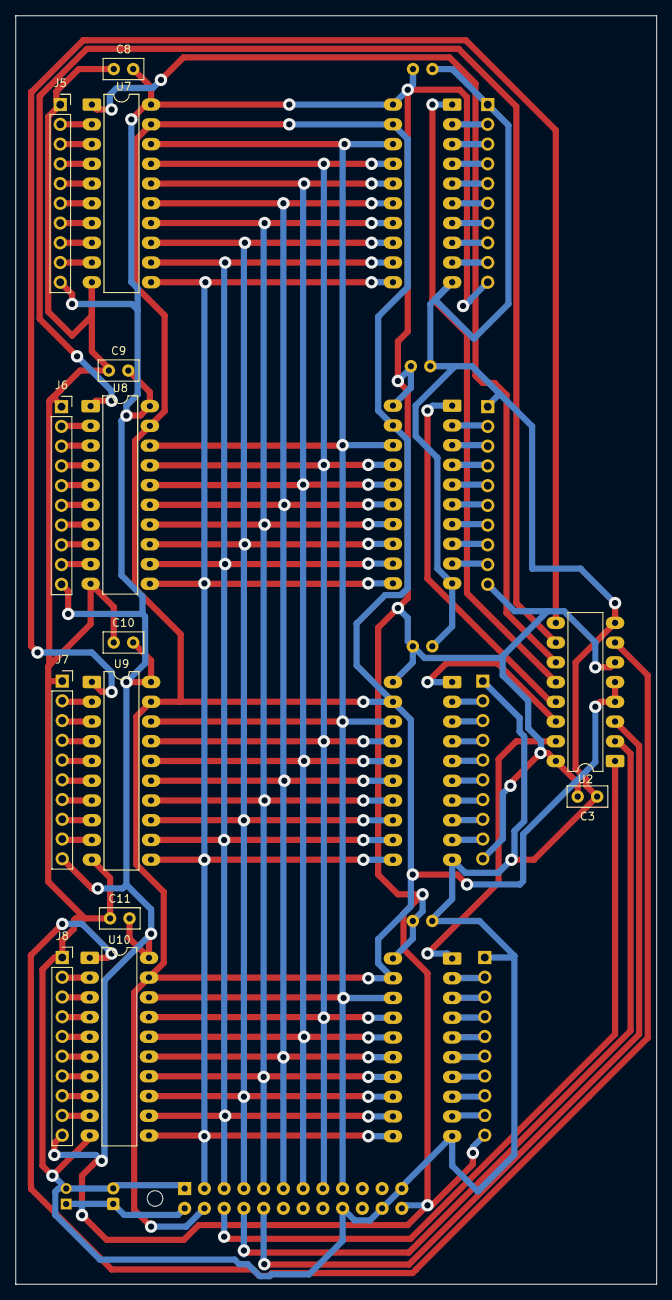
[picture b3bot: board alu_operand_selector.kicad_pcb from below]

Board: 2 copper layers, 82.5 x 163.2 mm, 29 parts (14 on the bottom side), 86 nets.
